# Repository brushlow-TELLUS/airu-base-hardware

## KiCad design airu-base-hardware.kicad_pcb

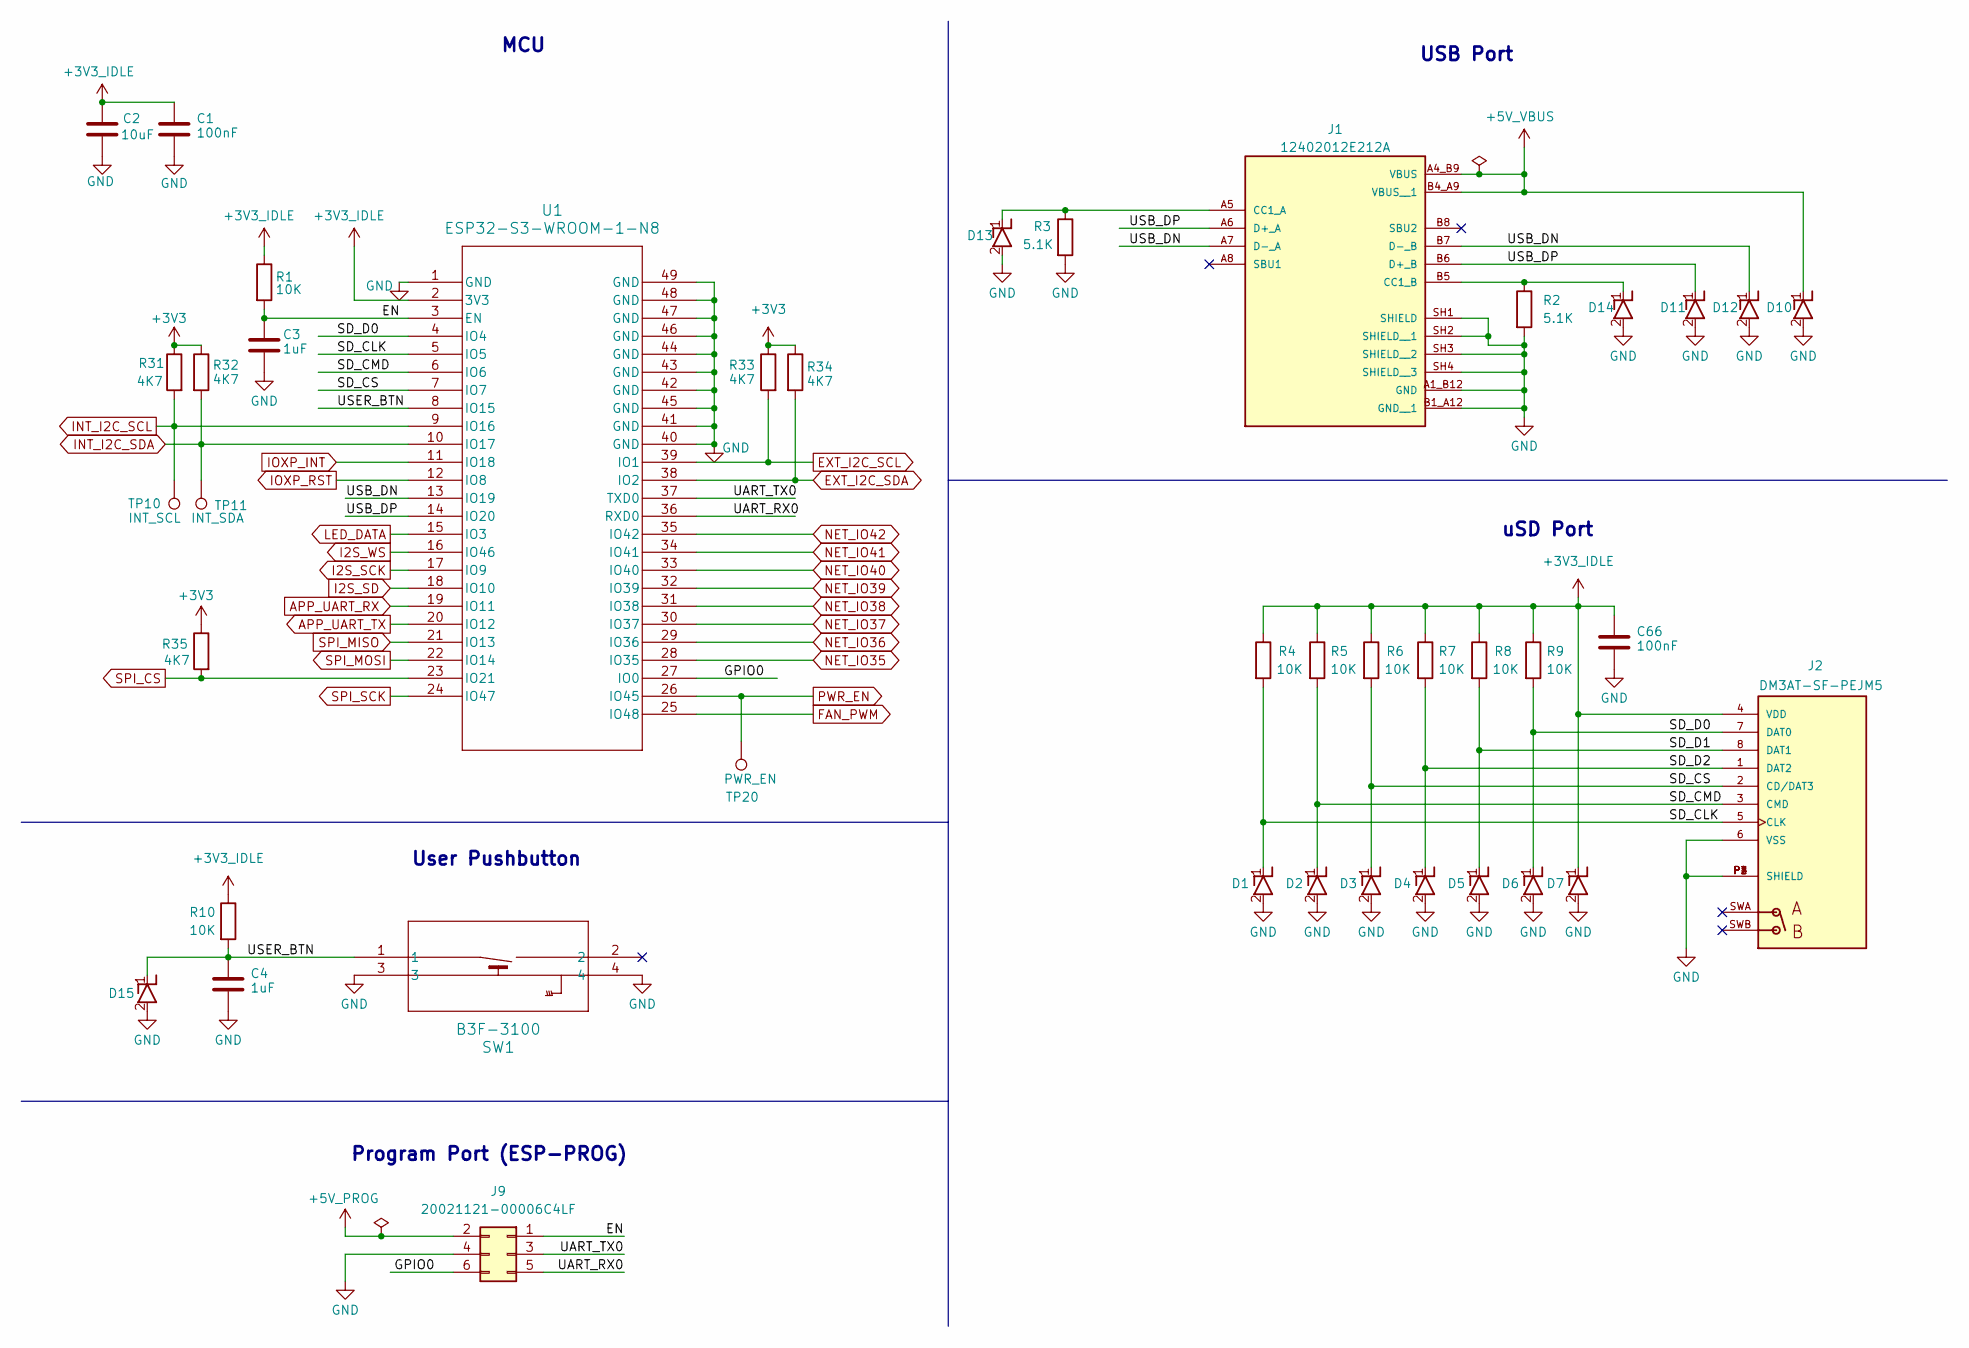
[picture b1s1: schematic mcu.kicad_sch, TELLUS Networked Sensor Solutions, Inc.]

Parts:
C1, C66: 100nF; C_0603_1608Metric; Manufacturer_PN CC0603KRX7R7BB104
C2: 10uF; C_0603_1608Metric; Manufacturer_PN CL10X106MO8NRNC
C3, C4: 1uF; C_0603_1608Metric; Manufacturer_PN CL10B105KP8NNNC
D1, D2, D3, D4, D5, D6, D7, D10, D11, D12, D13, D14, D15: D5V0F1U2LP-7B; D5V0F1U2LP7B; Manufacturer_Part_Number D5V0F1U2LP-7B; Mouser Part Number 621-D5V0F1U2LP7B
J1: 12402012E212A; AMPHENOL_12402012E212A; PARTREV 4
J2: DM3AT-SF-PEJM5; HRS_DM3AT-SF-PEJM5; Manufacturer_PN DM3AT-SF-PEJM5(11)
J9: 20021121-00006C4LF; CONN_20021121-00006C4LF_AMP; Manufacturer_PN 20021121-00006C4LF
R1, R4, R5, R6, R7, R8, R9, R10: 10K; R_0603_1608Metric; Manufacturer_PN RC0603FR-0710KL
R2, R3: 5.1K; R_0603_1608Metric; Manufacturer_PN RC0603FR-075K1L
R31, R32, R33, R34, R35: 4K7; R_0603_1608Metric; Manufacturer_PN RC0603FR-074K7L
SW1: B3F-3100; SW_B3F-3100_OMR; Manufacturer_PN B3F-3100
TP10: INT_SCL; TestPoint_Pad_1.0x1.0mm
TP11: INT_SDA; TestPoint_Pad_1.0x1.0mm
TP20: PWR_EN; TestPoint_Pad_1.0x1.0mm
U1: ESP32-S3-WROOM-1-N8; ESP32-S3-WROOM-1_EXP; Manufacturer_PN ESP32-S3-WROOM-1-N8

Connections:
+3V3: R31.1, R32.1, R33.1, R34.1, R35.1; also elsewhere on the board
+3V3_IDLE: C1.1, C2.1, C66.1, D7.1 (K), J2.4 (VDD), R1.1, R4.1, R5.1, R6.1, R7.1, R8.1, R9.1, R10.1, U1.2 (3V3); also elsewhere on the board
+5V_PROG: J9.2; also elsewhere on the board
+5V_VBUS: D10.1 (K), J1.A4_B9 (VBUS), J1.B4_A9 (VBUS__1); also elsewhere on the board
/MCU/EN: C3.1, J9.1, R1.2, U1.3 (EN)
/MCU/GPIO0: J9.6, U1.27 (IO0)
/MCU/SD_CLK: D1.1 (K), J2.5 (CLK), R4.2, U1.5 (IO5)
/MCU/SD_CMD: D2.1 (K), J2.3 (CMD), R5.2, U1.6 (IO6)
/MCU/SD_CS: D3.1 (K), J2.2 (CD/DAT3), R6.2, U1.7 (IO7)
/MCU/SD_D0: D6.1 (K), J2.7 (DAT0), R9.2, U1.4 (IO4)
/MCU/SD_D1: D5.1 (K), J2.8 (DAT1), R8.2
/MCU/SD_D2: D4.1 (K), J2.1 (DAT2), R7.2
/MCU/UART_RX0: J9.5, U1.36 (RXD0)
/MCU/UART_TX0: J9.3, U1.37 (TXD0)
/MCU/USB_DN: D12.1 (K), J1.A7 (D-_A), J1.B7 (D-_B), U1.13 (IO19)
/MCU/USB_DP: D11.1 (K), J1.A6 (D+_A), J1.B6 (D+_B), U1.14 (IO20)
/MCU/USER_BTN: C4.1, D15.1 (K), R10.2, SW1.1, U1.8 (IO15)
APP_UART_RX: U1.19 (IO11); also elsewhere on the board
APP_UART_TX: U1.20 (IO12); also elsewhere on the board
EXT_I2C_SCL: R33.2, U1.39 (IO1); also elsewhere on the board
EXT_I2C_SDA: R34.2, U1.38 (IO2); also elsewhere on the board
FAN_PWM: U1.25 (IO48); also elsewhere on the board
GND: C1.2, C2.2, C3.2, C4.2, C66.2, D1.2 (A), D2.2 (A), D3.2 (A), D4.2 (A), D5.2 (A), D6.2 (A), D7.2 (A), D10.2 (A), D11.2 (A), D12.2 (A), D13.2 (A), D14.2 (A), D15.2 (A), J1.A1_B12 (GND), J1.B1_A12 (GND__1), J1.SH1 (SHIELD), J1.SH2 (SHIELD__1), J1.SH3 (SHIELD__2), J1.SH4 (SHIELD__3), J2.6 (VSS), J2.P1 (SHIELD), J2.P2 (SHIELD), J2.P3 (SHIELD), J2.P4 (SHIELD), J9.4, R2.2, R3.2, SW1.3, SW1.4, U1.1 (GND), U1.40 (GND), U1.41 (GND), U1.42 (GND), U1.43 (GND), U1.44 (GND), U1.45 (GND), U1.46 (GND), U1.47 (GND), U1.48 (GND), U1.49 (GND); also elsewhere on the board
I2S_SCK: U1.17 (IO9); also elsewhere on the board
I2S_SD: U1.18 (IO10); also elsewhere on the board
I2S_WS: U1.16 (IO46); also elsewhere on the board
INT_I2C_SCL: R31.2, TP10.1, U1.9 (IO16); also elsewhere on the board
INT_I2C_SDA: R32.2, TP11.1, U1.10 (IO17); also elsewhere on the board
IOXP_INT: U1.11 (IO18); also elsewhere on the board
IOXP_RST: U1.12 (IO8); also elsewhere on the board
LED_DATA: U1.15 (IO3); also elsewhere on the board
NET_IO35: U1.28 (IO35); also elsewhere on the board
NET_IO36: U1.29 (IO36); also elsewhere on the board
NET_IO37: U1.30 (IO37); also elsewhere on the board
NET_IO38: U1.31 (IO38); also elsewhere on the board
NET_IO39: U1.32 (IO39); also elsewhere on the board
NET_IO40: U1.33 (IO40); also elsewhere on the board
NET_IO41: U1.34 (IO41); also elsewhere on the board
NET_IO42: U1.35 (IO42); also elsewhere on the board
unnamed: D13.1 (K), J1.A5 (CC1_A), R3.1
unnamed: D14.1 (K), J1.B5 (CC1_B), R2.1
PWR_EN: TP20.1, U1.26 (IO45); also elsewhere on the board
SPI_CS: R35.2, U1.23 (IO21); also elsewhere on the board
SPI_MISO: U1.21 (IO13); also elsewhere on the board
SPI_MOSI: U1.22 (IO14); also elsewhere on the board
SPI_SCK: U1.24 (IO47); also elsewhere on the board

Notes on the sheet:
Program Port (ESP-PROG)
User Pushbutton
USB Port
MCU
uSD Port

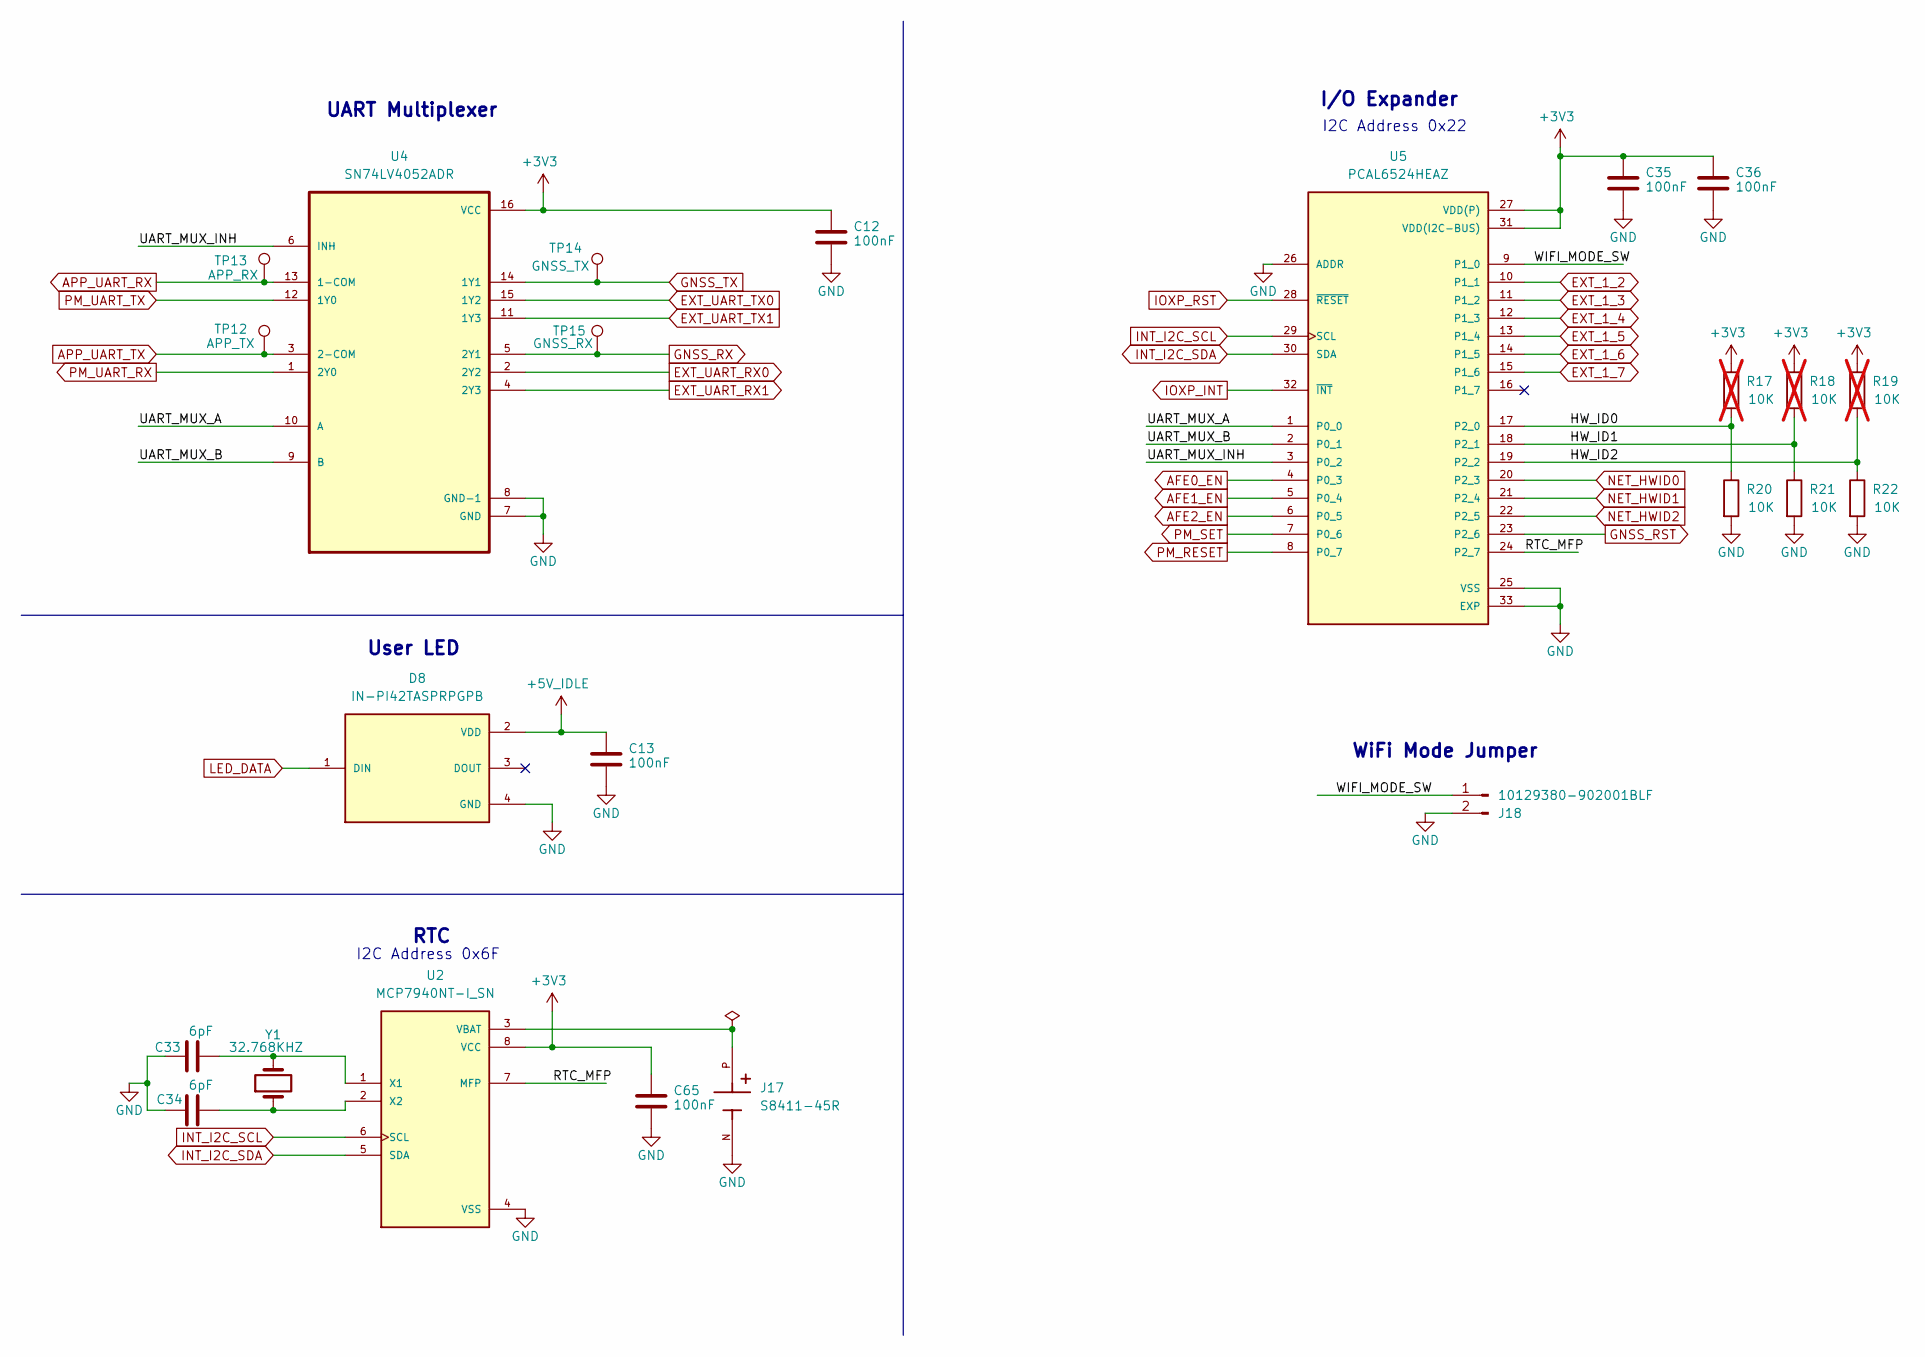
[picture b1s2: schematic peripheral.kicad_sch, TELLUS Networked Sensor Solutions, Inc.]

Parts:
C12, C13, C35, C36, C65: 100nF; C_0603_1608Metric; Manufacturer_PN CC0603KRX7R7BB104
C33, C34: 6pF; C_0603_1608Metric; Manufacturer_PN CC0603DRNPO9BN6R0
D8: IN-PI42TASPRPGPB; LED_IN-PI42TASPRPGPB; PARTREV Oct. 10, 2021
J17: S8411-45R; HARWIN_S8411-45R; PARTREV 4
J18: 10129380-902001BLF; AMPHENOL_10129380-902001BLF; Manufacturer_PN 10129380-902001BLF
R17, R18, R19: 10K; R_0603_1608Metric; not fitted
R20, R21, R22: 10K; R_0603_1608Metric; Manufacturer_PN RC0603FR-0710KL
TP12: APP_TX; TestPoint_Pad_1.0x1.0mm
TP13: APP_RX; TestPoint_Pad_1.0x1.0mm
TP14: GNSS_TX; TestPoint_Pad_1.0x1.0mm
TP15: GNSS_RX; TestPoint_Pad_1.0x1.0mm
U2: MCP7940NT-I_SN; SOIC127P600X175-8N; PARTREV G
U4: SN74LV4052ADR; SOIC127P600X175-16N; Manufacturer_PN SN74LV4052ADR
U5: PCAL6524HEAZ; IC_PCAL6524HEAZ; Manufacturer_PN PCAL6524HEAZ
Y1: 32.768KHZ; XTAL_MU00525_NDK; Manufactuer_PN MU00525-32.768K

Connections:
+3V3: C12.1, C35.1, C36.1, C65.1, R17.1, R18.1, R19.1, U2.8 (VCC), U4.16 (VCC), U5.27 (VDD(P)), U5.31 (VDD(I2C-BUS)); also elsewhere on the board
+5V_IDLE: C13.1, D8.2 (VDD); also elsewhere on the board
/Peripheral/HW_ID0: R17.2, R20.1, U5.17 (P2_0)
/Peripheral/HW_ID1: R18.2, R21.1, U5.18 (P2_1)
/Peripheral/HW_ID2: R19.2, R22.1, U5.19 (P2_2)
/Peripheral/RTC_MFP: U2.7 (MFP), U5.24 (P2_7)
/Peripheral/UART_MUX_A: U4.10 (A), U5.1 (P0_0)
/Peripheral/UART_MUX_B: U4.9 (B), U5.2 (P0_1)
/Peripheral/UART_MUX_INH: U4.6 (INH), U5.3 (P0_2)
/Peripheral/WIFI_MODE_SW: J18.1, U5.9 (P1_0)
AFE0_EN: U5.4 (P0_3); also elsewhere on the board
AFE1_EN: U5.5 (P0_4); also elsewhere on the board
AFE2_EN: U5.6 (P0_5); also elsewhere on the board
APP_UART_RX: TP13.1, U4.13 (1-COM); also elsewhere on the board
APP_UART_TX: TP12.1, U4.3 (2-COM); also elsewhere on the board
EXT_1_2: U5.10 (P1_1); also elsewhere on the board
EXT_1_3: U5.11 (P1_2); also elsewhere on the board
EXT_1_4: U5.12 (P1_3); also elsewhere on the board
EXT_1_5: U5.13 (P1_4); also elsewhere on the board
EXT_1_6: U5.14 (P1_5); also elsewhere on the board
EXT_1_7: U5.15 (P1_6); also elsewhere on the board
EXT_UART_RX0: U4.2 (2Y2); also elsewhere on the board
EXT_UART_RX1: U4.4 (2Y3); also elsewhere on the board
EXT_UART_TX0: U4.15 (1Y2); also elsewhere on the board
EXT_UART_TX1: U4.11 (1Y3); also elsewhere on the board
GND: C12.2, C13.2, C33.1, C34.1, C35.2, C36.2, C65.2, D8.4 (GND), J17.N, J18.2, R20.2, R21.2, R22.2, U2.4 (VSS), U4.7 (GND), U4.8 (GND-1), U5.25 (VSS), U5.26 (ADDR), U5.33 (EXP); also elsewhere on the board
GNSS_RST: U5.23 (P2_6); also elsewhere on the board
GNSS_RX: TP15.1, U4.5 (2Y1); also elsewhere on the board
GNSS_TX: TP14.1, U4.14 (1Y1); also elsewhere on the board
INT_I2C_SCL: U2.6 (SCL), U5.29 (SCL); also elsewhere on the board
INT_I2C_SDA: U2.5 (SDA), U5.30 (SDA); also elsewhere on the board
IOXP_INT: U5.32 (~INT); also elsewhere on the board
IOXP_RST: U5.28 (~RESET); also elsewhere on the board
LED_DATA: D8.1 (DIN); also elsewhere on the board
NET_HWID0: U5.20 (P2_3); also elsewhere on the board
NET_HWID1: U5.21 (P2_4); also elsewhere on the board
NET_HWID2: U5.22 (P2_5); also elsewhere on the board
unnamed: J17.P, U2.3 (VBAT)
unnamed: C33.2, U2.1 (X1), Y1.2
unnamed: C34.2, U2.2 (X2), Y1.1
PM_RESET: U5.8 (P0_7); also elsewhere on the board
PM_SET: U5.7 (P0_6); also elsewhere on the board
PM_UART_RX: U4.1 (2Y0); also elsewhere on the board
PM_UART_TX: U4.12 (1Y0); also elsewhere on the board

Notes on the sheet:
I/O Expander
UART Multiplexer
WiFi Mode Jumper
User LED
RTC
I2C Address 0x22
I2C Address 0x6F

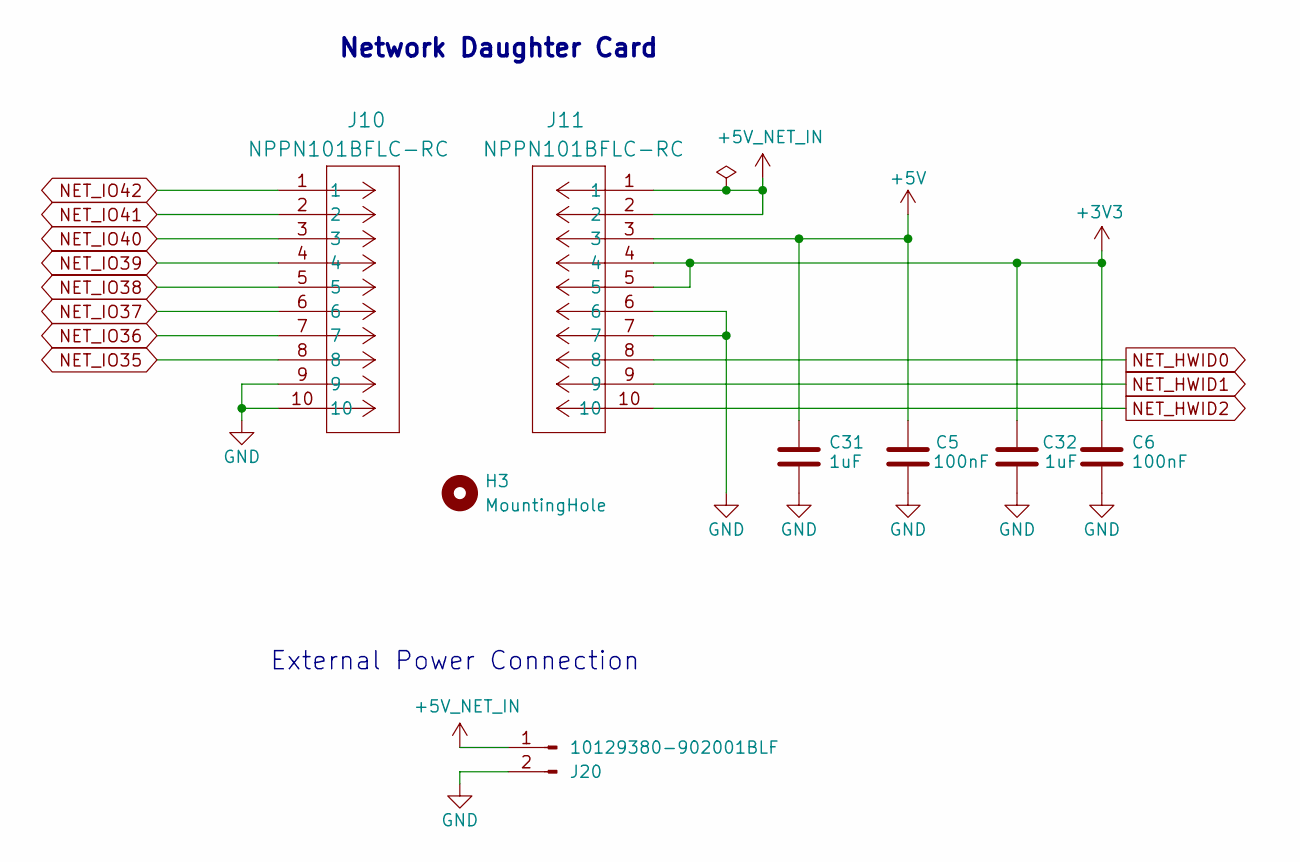
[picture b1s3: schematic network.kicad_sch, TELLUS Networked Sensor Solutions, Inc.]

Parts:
C5, C6: 100nF; C_0603_1608Metric; Manufacturer_PN CC0603KRX7R7BB104
C31, C32: 1uF; C_0603_1608Metric; Manufacturer_PN CL10B105KP8NNNC
H3: MountingHole; MountingHole_2.7mm
J10, J11: NPPN101BFLC-RC; CONN10X1_NPPN101BFLC-RC_SUL; Manufacturer_PN NPPN101BFLC-RC
J20: 10129380-902001BLF; AMPHENOL_10129380-902001BLF; Manufacturer_PN 10129380-902001BLF

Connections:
+3V3: C6.1, C32.1, J11.4, J11.5; also elsewhere on the board
+5V: C5.1, C31.1, J11.3; also elsewhere on the board
+5V_NET_IN: J11.1, J11.2, J20.1; also elsewhere on the board
GND: C5.2, C6.2, C31.2, C32.2, J10.9, J10.10, J11.6, J11.7, J20.2; also elsewhere on the board
NET_HWID0: J11.8; also elsewhere on the board
NET_HWID1: J11.9; also elsewhere on the board
NET_HWID2: J11.10; also elsewhere on the board
NET_IO35: J10.8; also elsewhere on the board
NET_IO36: J10.7; also elsewhere on the board
NET_IO37: J10.6; also elsewhere on the board
NET_IO38: J10.5; also elsewhere on the board
NET_IO39: J10.4; also elsewhere on the board
NET_IO40: J10.3; also elsewhere on the board
NET_IO41: J10.2; also elsewhere on the board
NET_IO42: J10.1; also elsewhere on the board

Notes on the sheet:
External Power Connection
Network Daughter Card

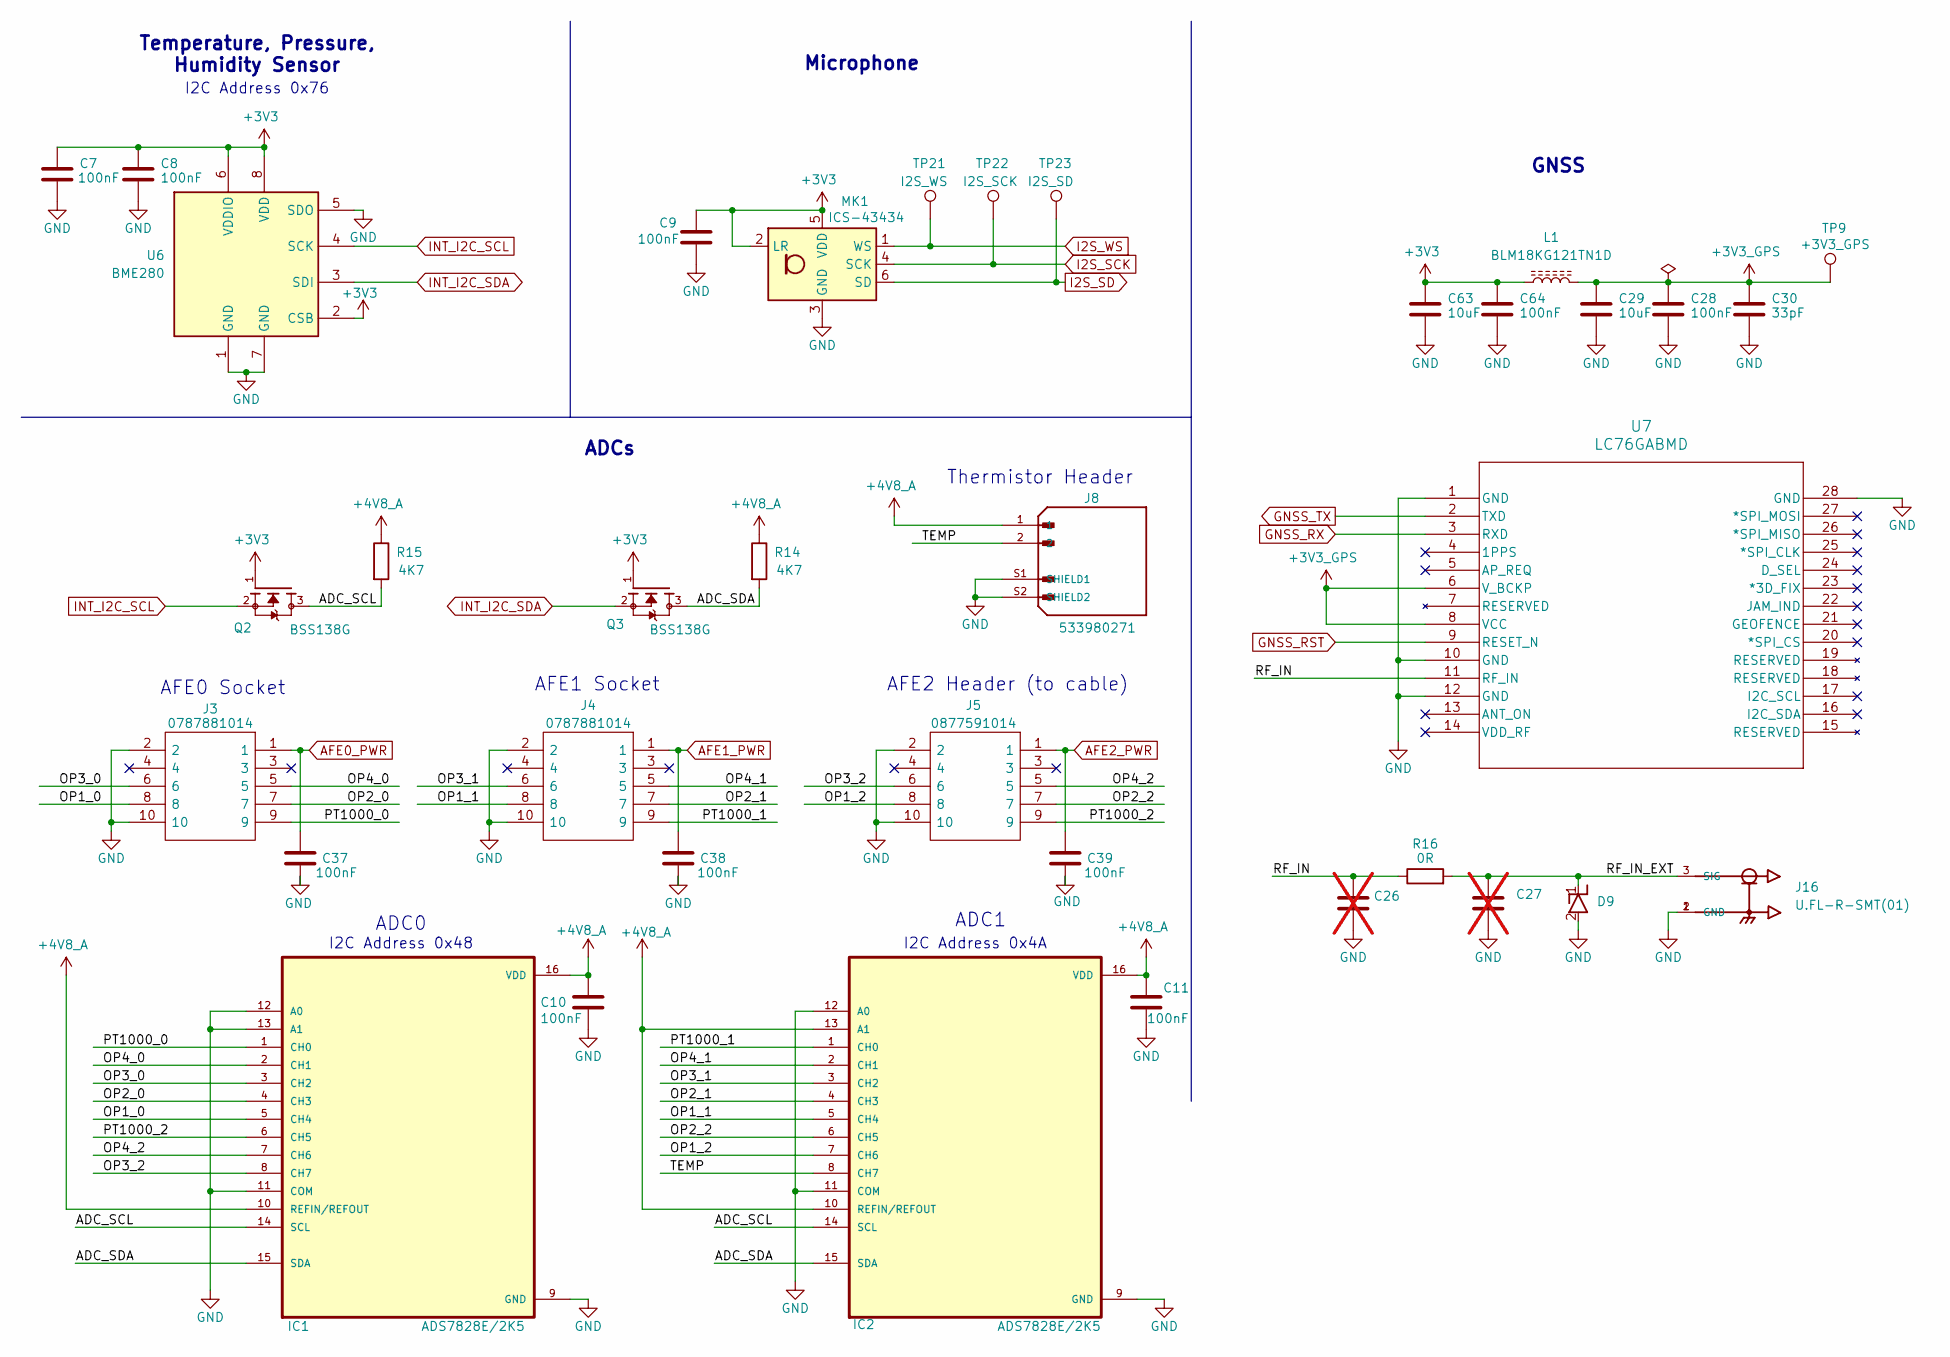
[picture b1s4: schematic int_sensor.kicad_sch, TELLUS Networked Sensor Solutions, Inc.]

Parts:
C7, C8, C9, C10, C11, C28, C37, C38, C39, C64: 100nF; C_0603_1608Metric; Manufacturer_PN CC0603KRX7R7BB104
C26, C27: C; C_0402_1005Metric; not fitted
C29, C63: 10uF; C_0603_1608Metric; Manufacturer_PN CL10X106MO8NRNC
C30: 33pF; C_0603_1608Metric; Manufacturer_PN C0603C330J5GACTU
D9: D5V0F1U2LP-7B; D5V0F1U2LP7B; Manufacturer_Part_Number D5V0F1U2LP-7B; Mouser Part Number 621-D5V0F1U2LP7B
IC1, IC2: ADS7828E/2K5; SOP65P640X120-16N; Manufacturer_PN ADS7828E/2K5
J3, J4: 0787881014; ALPHASENSE_AFE_2; Manufacturer_Part_Number 0787881014
J5: 0877591014; CONN10_877591014_MOL; Manufacturer_PN 0877591014
J8: 533980271; MOLEX_533980271; PARTREV A
J16: U.FL-R-SMT(01); HRS_U.FL-R-SMT(01); Manufacturer_PN U.FL-R-SMT(01)
L1: BLM18KG121TN1D; R_0603_1608Metric; Manufacturer_PN BLM18KG121TN1D
MK1: ICS-43434; InvenSense_ICS-43434-6_3.5x2.65mm; Manufacturer_PN ICS-43434
Q2, Q3: BSS138G; SOT95P240X111-3N; PARTREV 30 Jan 2018
R14, R15: 4K7; R_0603_1608Metric; Manufacturer_PN RC0603FR-074K7L
R16: 0R; R_0402_1005Metric; Manufacturer_PN RC0402JR-070RL
TP9: +3V3_GPS; TestPoint_Pad_1.0x1.0mm
TP21: I2S_WS; TestPoint_Pad_1.0x1.0mm
TP22: I2S_SCK; TestPoint_Pad_1.0x1.0mm
TP23: I2S_SD; TestPoint_Pad_1.0x1.0mm
U6: BME280; Bosch_LGA-8_2.5x2.5mm_P0.65mm_ClockwisePinNumbering; Manufacturer_PN BME280
U7: LC76GABMD; LC76G_QWS; Manufacturer_PN LC76GABMD

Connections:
+3V3: C7.1, C8.1, C9.1, C63.1, C64.1, L1.1, MK1.2 (LR), MK1.5 (VDD), Q2.1, Q3.1, U6.2 (CSB), U6.6 (VDDIO), U6.8 (VDD); also elsewhere on the board
+3V3_GPS: C28.1, C29.1, C30.1, L1.2, TP9.1, U7.6 (V_BCKP), U7.8 (VCC)
+4V8_A: C10.1, C11.1, IC1.10 (REFIN/REFOUT), IC1.16 (VDD), IC2.10 (REFIN/REFOUT), IC2.13 (A1), IC2.16 (VDD), J8.1, R14.1, R15.1; also elsewhere on the board
/Internal Sensor/ADC_SCL: IC1.14 (SCL), IC2.14 (SCL), Q2.3, R15.2
/Internal Sensor/ADC_SDA: IC1.15 (SDA), IC2.15 (SDA), Q3.3, R14.2
/Internal Sensor/OP1_0: IC1.5 (CH4), J3.8
/Internal Sensor/OP1_1: IC2.5 (CH4), J4.8
/Internal Sensor/OP1_2: IC2.7 (CH6), J5.8
/Internal Sensor/OP2_0: IC1.4 (CH3), J3.7
/Internal Sensor/OP2_1: IC2.4 (CH3), J4.7
/Internal Sensor/OP2_2: IC2.6 (CH5), J5.7
/Internal Sensor/OP3_0: IC1.3 (CH2), J3.6
/Internal Sensor/OP3_1: IC2.3 (CH2), J4.6
/Internal Sensor/OP3_2: IC1.8 (CH7), J5.6
/Internal Sensor/OP4_0: IC1.2 (CH1), J3.5
/Internal Sensor/OP4_1: IC2.2 (CH1), J4.5
/Internal Sensor/OP4_2: IC1.7 (CH6), J5.5
/Internal Sensor/PT1000_0: IC1.1 (CH0), J3.9
/Internal Sensor/PT1000_1: IC2.1 (CH0), J4.9
/Internal Sensor/PT1000_2: IC1.6 (CH5), J5.9
/Internal Sensor/RF_IN: C26.1, R16.1, U7.11 (RF_IN)
/Internal Sensor/RF_IN_EXT: C27.1, D9.1 (K), J16.3 (SIG), R16.2
/Internal Sensor/TEMP: IC2.8 (CH7), J8.2
AFE0_PWR: C37.1, J3.1; also elsewhere on the board
AFE1_PWR: C38.1, J4.1; also elsewhere on the board
AFE2_PWR: C39.1, J5.1; also elsewhere on the board
GND: C7.2, C8.2, C9.2, C10.2, C11.2, C26.2, C27.2, C28.2, C29.2, C30.2, C37.2, C38.2, C39.2, C63.2, C64.2, D9.2 (A), IC1.9 (GND), IC1.11 (COM), IC1.12 (A0), IC1.13 (A1), IC2.9 (GND), IC2.11 (COM), IC2.12 (A0), J3.2, J3.10, J4.2, J4.10, J5.2, J5.10, J8.S1 (SHIELD1), J8.S2 (SHIELD2), J16.1 (GND), J16.2 (GND), MK1.3 (GND), U6.1 (GND), U6.5 (SDO), U6.7 (GND), U7.1 (GND), U7.10 (GND), U7.12 (GND), U7.28 (GND); also elsewhere on the board
GNSS_RST: U7.9 (RESET_N); also elsewhere on the board
GNSS_RX: U7.3 (RXD); also elsewhere on the board
GNSS_TX: U7.2 (TXD); also elsewhere on the board
I2S_SCK: MK1.4 (SCK), TP22.1; also elsewhere on the board
I2S_SD: MK1.6 (SD), TP23.1; also elsewhere on the board
I2S_WS: MK1.1 (WS), TP21.1; also elsewhere on the board
INT_I2C_SCL: Q2.2, U6.4 (SCK); also elsewhere on the board
INT_I2C_SDA: Q3.2, U6.3 (SDI); also elsewhere on the board

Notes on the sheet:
GNSS
I2C Address 0x48
ADC0
ADCs
I2C Address 0x4A
Temperature, Pressure, Humidity Sensor
ADC1
Microphone
Thermistor Header
AFE1 Socket
AFE2 Header (to cable)
I2C Address 0x76
AFE0 Socket

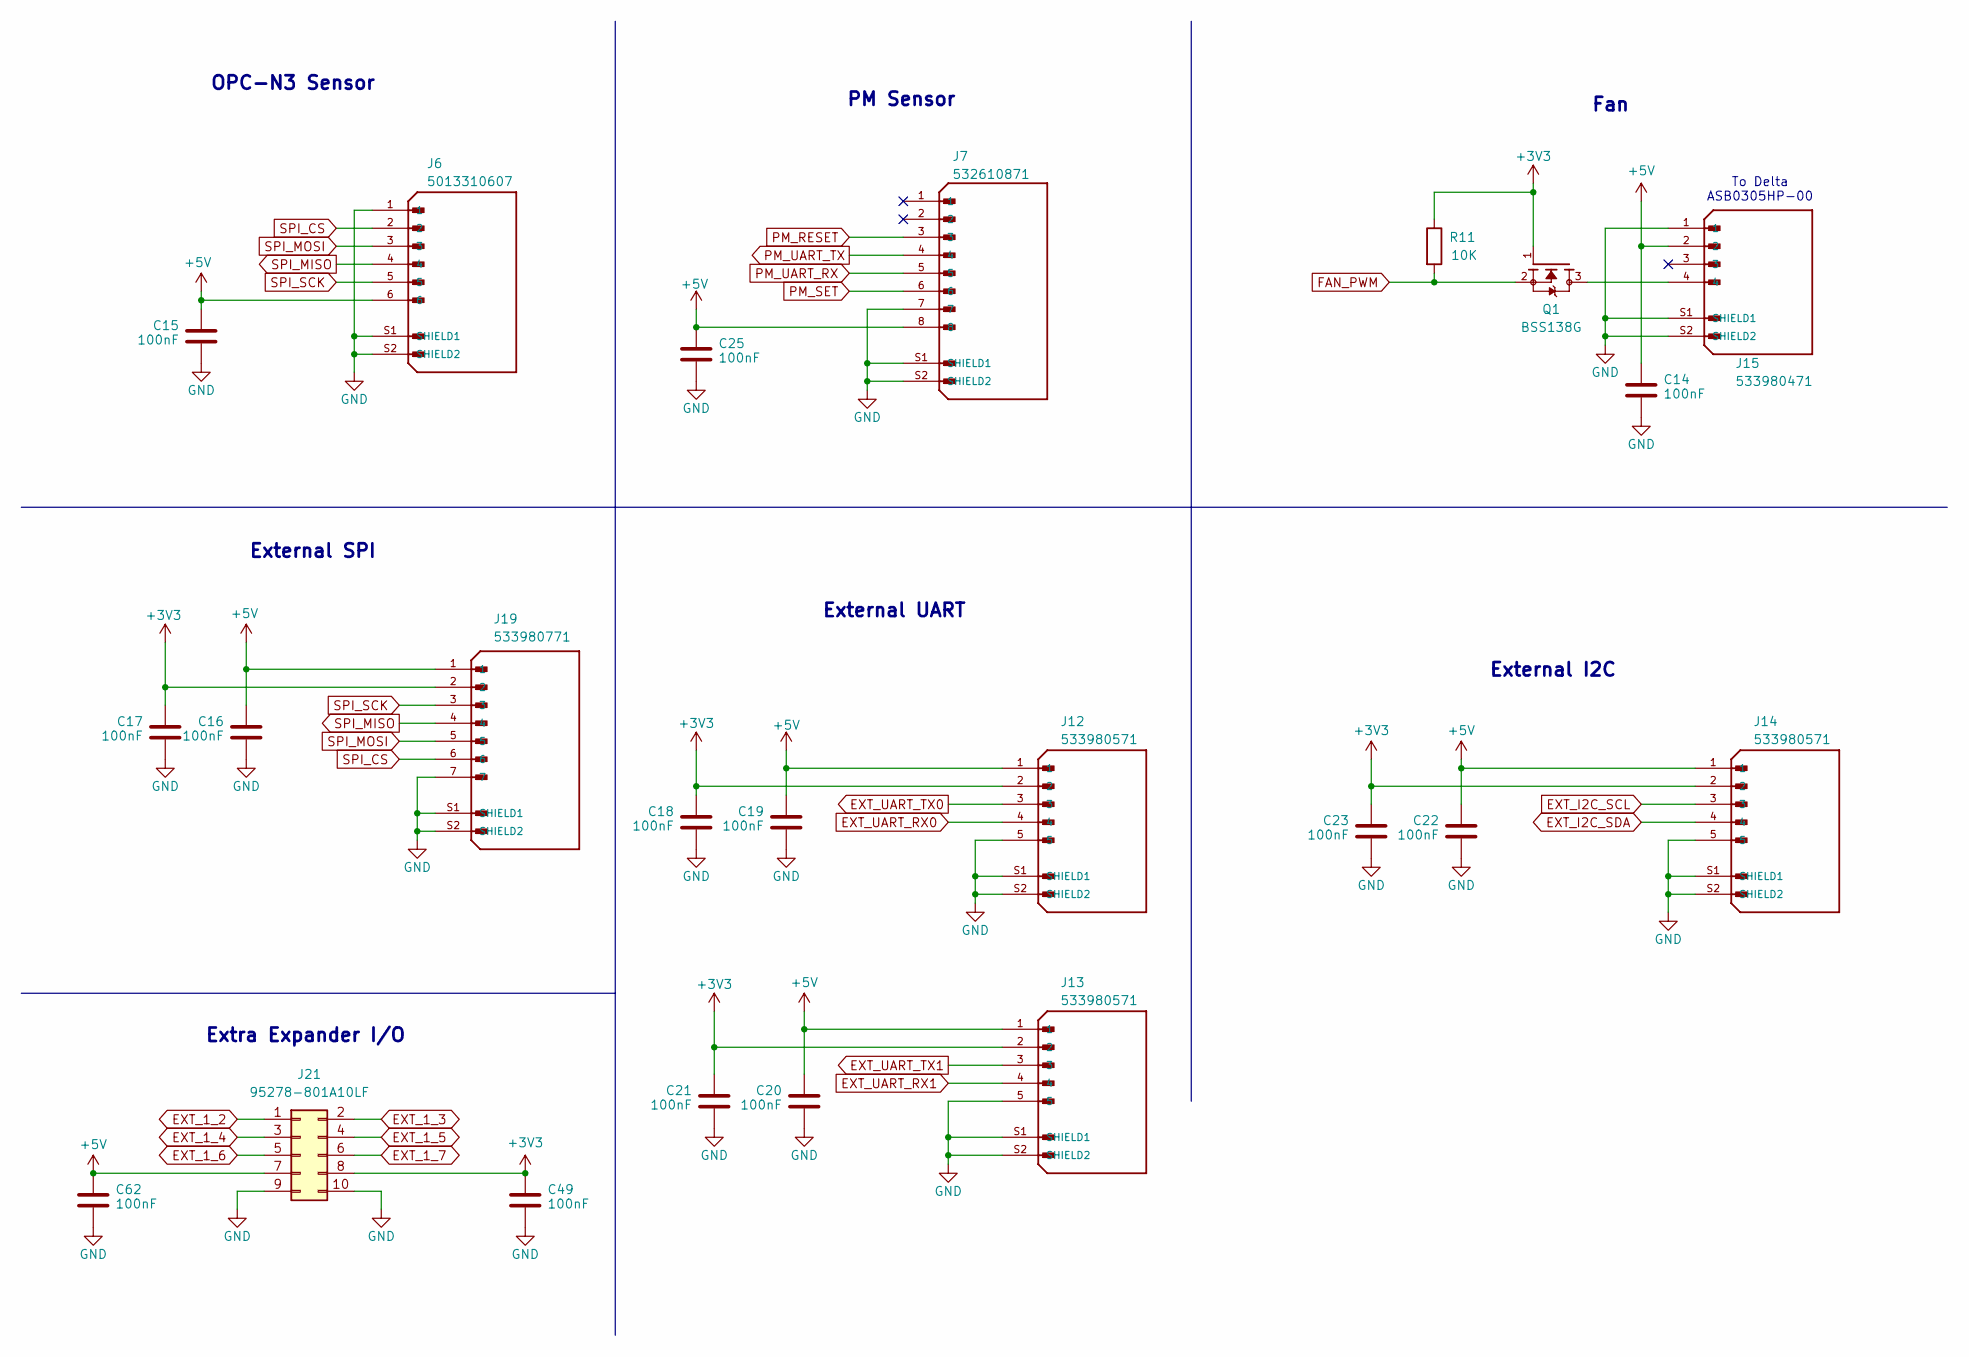
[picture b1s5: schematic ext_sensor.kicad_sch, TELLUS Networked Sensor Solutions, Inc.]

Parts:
C14, C15, C16, C17, C18, C19, C20, C21, C22, C23, C25, C49, C62: 100nF; C_0603_1608Metric; Manufacturer_PN CC0603KRX7R7BB104
J6: 5013310607; MOLEX_5013310607; PARTREV A
J7: 532610871; MOLEX_53261-0871; PARTREV J
J12, J13, J14: 533980571; MOLEX_533980571; PARTREV A
J15: 533980471; MOLEX_533980471; PARTREV A
J19: 533980771; MOLEX_533980771; PARTREV A
J21: 95278-801A10LF; CONN_95278-801A10LF_AMP; Manufacturer_PN 95278-801A10LF
Q1: BSS138G; SOT95P240X111-3N; PARTREV 30 Jan 2018
R11: 10K; R_0603_1608Metric; Manufacturer_PN RC0603FR-0710KL

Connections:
+3V3: C17.1, C18.1, C21.1, C23.1, C49.1, J12.2, J13.2, J14.2, J19.2, J21.8, Q1.1, R11.1; also elsewhere on the board
+5V: C14.1, C15.1, C16.1, C19.1, C20.1, C22.1, C25.1, C62.1, J6.6, J7.8, J12.1, J13.1, J14.1, J15.2, J19.1, J21.7; also elsewhere on the board
EXT_1_2: J21.1; also elsewhere on the board
EXT_1_3: J21.2; also elsewhere on the board
EXT_1_4: J21.3; also elsewhere on the board
EXT_1_5: J21.4; also elsewhere on the board
EXT_1_6: J21.5; also elsewhere on the board
EXT_1_7: J21.6; also elsewhere on the board
EXT_I2C_SCL: J14.3; also elsewhere on the board
EXT_I2C_SDA: J14.4; also elsewhere on the board
EXT_UART_RX0: J12.4; also elsewhere on the board
EXT_UART_RX1: J13.4; also elsewhere on the board
EXT_UART_TX0: J12.3; also elsewhere on the board
EXT_UART_TX1: J13.3; also elsewhere on the board
FAN_PWM: Q1.2, R11.2; also elsewhere on the board
GND: C14.2, C15.2, C16.2, C17.2, C18.2, C19.2, C20.2, C21.2, C22.2, C23.2, C25.2, C49.2, C62.2, J6.1, J6.S1 (SHIELD1), J6.S2 (SHIELD2), J7.7, J7.S1 (SHIELD1), J7.S2 (SHIELD2), J12.5, J12.S1 (SHIELD1), J12.S2 (SHIELD2), J13.5, J13.S1 (SHIELD1), J13.S2 (SHIELD2), J14.5, J14.S1 (SHIELD1), J14.S2 (SHIELD2), J15.1, J15.S1 (SHIELD1), J15.S2 (SHIELD2), J19.7, J19.S1 (SHIELD1), J19.S2 (SHIELD2), J21.9, J21.10; also elsewhere on the board
unnamed: J15.4, Q1.3
PM_RESET: J7.3; also elsewhere on the board
PM_SET: J7.6; also elsewhere on the board
PM_UART_RX: J7.5; also elsewhere on the board
PM_UART_TX: J7.4; also elsewhere on the board
SPI_CS: J6.2, J19.6; also elsewhere on the board
SPI_MISO: J6.4, J19.4; also elsewhere on the board
SPI_MOSI: J6.3, J19.5; also elsewhere on the board
SPI_SCK: J6.5, J19.3; also elsewhere on the board

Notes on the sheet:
External SPI
External UART
PM Sensor
External I2C
Extra Expander I/O
Fan
OPC-N3 Sensor
To Delta ASB0305HP-00
